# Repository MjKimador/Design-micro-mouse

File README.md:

This project includes two subsystems.
The power subsytem has files named with the suffix Power.
The sensing subsystems has files named with suffix Sensing.
There are two branches through which changes are made and the main branch holds files for both sensing subsystem and power subsystem.

For the Power Subsystem:
This system has been designed to provide power to the micro mouse system. It is designed using kiCad and to open the file you can open the .pro file and you will haev the entire project including the pcb files and schematic. The files used for ordering which inlude BOM files and all other files are not included in this folder but the project has all fields filled makingh it possible for all required files to be opened with ease.

For the Sensing Subsystem:
The subsystem serves as the sensory "eyes" of the micromouse, detecting obstacles in its path and facilitating navigation. It integrates easily with other features, ensuring efficient power usage and reliable obstacle detection within budgetary constraints.The design was done using kicad .The documents included are pcb ,schenatic and datasheet of components used.

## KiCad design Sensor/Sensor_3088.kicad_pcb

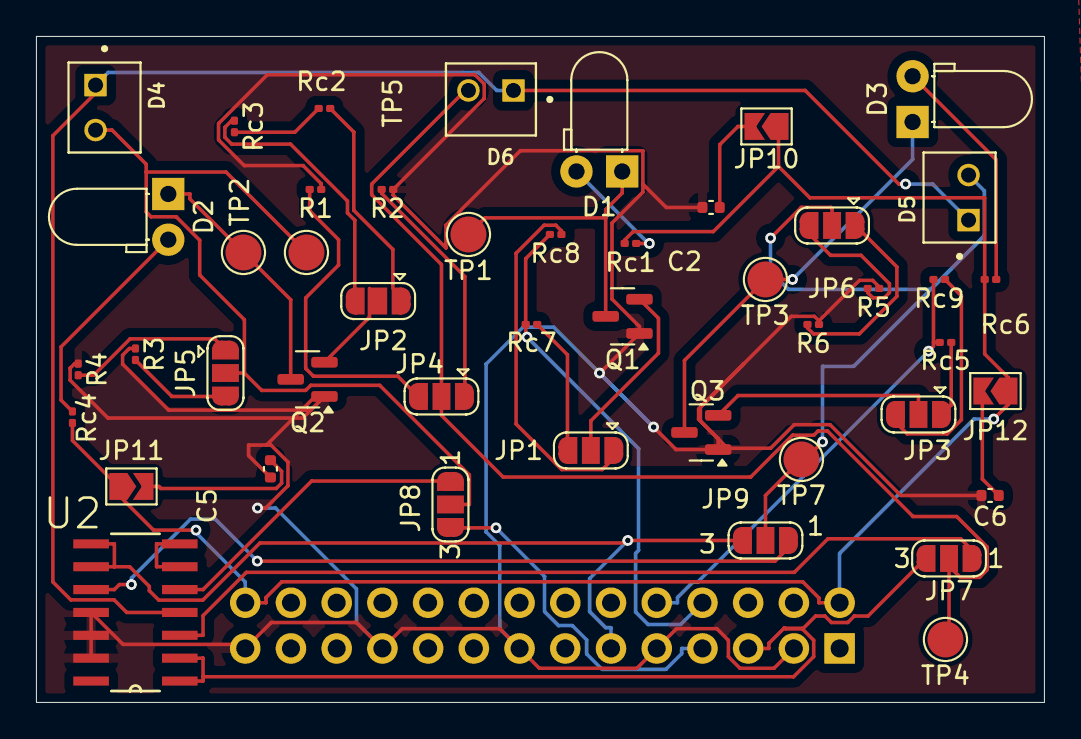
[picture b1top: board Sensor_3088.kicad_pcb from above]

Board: 2 copper layers, 56.0 x 37.0 mm, 47 parts (1 on the bottom side), 40 nets.

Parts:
C2, C5, C6: 10n; C_0402_1005Metric
D1, D2, D3: TSAL4400; LED_D3.0mm_Horizontal_O1.27mm_Z2.0mm_IRBlack
D4, D5, D6: BPW41N; DIO_BPW41N
J2: Conn_02x14_Odd_Even; PinHeader_2x14_P2.54mm_Vertical
JP1, JP2, JP3, JP4, JP5, JP6: SolderJumper_3_Open; SolderJumper-3_P1.3mm_Open_RoundedPad1.0x1.5mm
JP7, JP8, JP9: SolderJumper_3_Open; SolderJumper-3_P1.3mm_Open_RoundedPad1.0x1.5mm_NumberLabels
JP10, JP11, JP12: SolderJumper_2_Open; SolderJumper-2_P1.3mm_Open_TrianglePad1.0x1.5mm
Q1, Q2, Q3: SS8050; SOT-23
R1, R3, R5: 10k; R_0201_0603Metric
R2, R4, R6: 150k; R_0201_0603Metric
Rc1, Rc4, Rc6: 20; R_0201_0603Metric
Rc2, Rc5, Rc8: 1k; R_0201_0603Metric
Rc3, Rc7, Rc9: 470; R_0201_0603Metric
TP1, TP2, TP3, TP4, TP5, TP7: TestPoint; TestPoint_Pad_D2.0mm
U2: LM324DT; SOIC127P600X175-14N

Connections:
3V3: J2.2, J2.28, JP10.1 (A), JP11.1 (A), JP12.1 (A), Rc1.2, Rc4.2, Rc6.2
+3V3: D4.C, D5.C, D6.C, U2.4 (VCC+)
GND: C2.2, C5.2, C6.2, J2.3, J2.9, J2.15, J2.21, J2.27, Q1.1 (E), Q2.1 (E), Q3.1 (E), R1.1, R2.1, R3.1, R4.1, R5.1, R6.1, U2.11 (VCC-), U2.12 (POS_4), U2.13 (NEG_4)
unnamed: D1.2 (A), Rc1.1
unnamed: D1.1 (K), Q1.3 (C), TP1.1
unnamed: D2.2 (A), Rc4.1
unnamed: D2.1 (K), Q2.3 (C), TP2.1
unnamed: D3.2 (A), Rc6.1
unnamed: D3.1 (K), Q3.3 (C), TP3.1
unnamed: JP1.1 (A), Rc8.1
unnamed: JP1.3 (B), Rc7.1
unnamed: JP1.2 (C), Q1.2 (B)
unnamed: JP2.1 (A), Rc2.1
unnamed: JP2.3 (B), Rc3.1
unnamed: JP2.2 (C), Q2.2 (B)
unnamed: JP3.1 (A), Rc5.1
unnamed: JP3.3 (B), Rc9.1
unnamed: JP3.2 (C), Q3.2 (B)
unnamed: JP4.1 (A), R2.2
unnamed: JP4.3 (B), R1.2
unnamed: JP5.1 (A), R4.2
unnamed: JP5.3 (B), R3.2
unnamed: JP6.1 (A), R6.2
unnamed: JP6.3 (B), R5.2
unnamed: C2.1, JP10.2 (B)
unnamed: C5.1, JP11.2 (B)
unnamed: C6.1, JP12.2 (B)
unnamed: U2.6 (NEG_2), U2.7 (OUT2)
OUT1: D6.A, JP4.2 (C), JP7.2 (C), TP4.1
Output2: D4.A, JP5.2 (C), JP8.2 (C), TP5.1
Output3: D5.A, JP6.2 (C), JP9.2 (C), TP7.1
PA3: J2.5, JP7.3 (B), U2.1 (OUT1), U2.2 (NEG_1)
PA4: J2.7, JP8.3 (B)
PA5: J2.11, JP9.3 (B), U2.8 (OUT3), U2.9 (NEG3)
PE13: Rc2.2, Rc3.2
PE14: J2.10, Rc5.2, Rc9.2
PE15: J2.8, Rc7.2, Rc8.2
POS1: JP7.1 (A), U2.3 (POS_1)
POS2: JP8.1 (A), U2.5 (POS_2)
POS3: JP9.1 (A), U2.10 (POS_3)

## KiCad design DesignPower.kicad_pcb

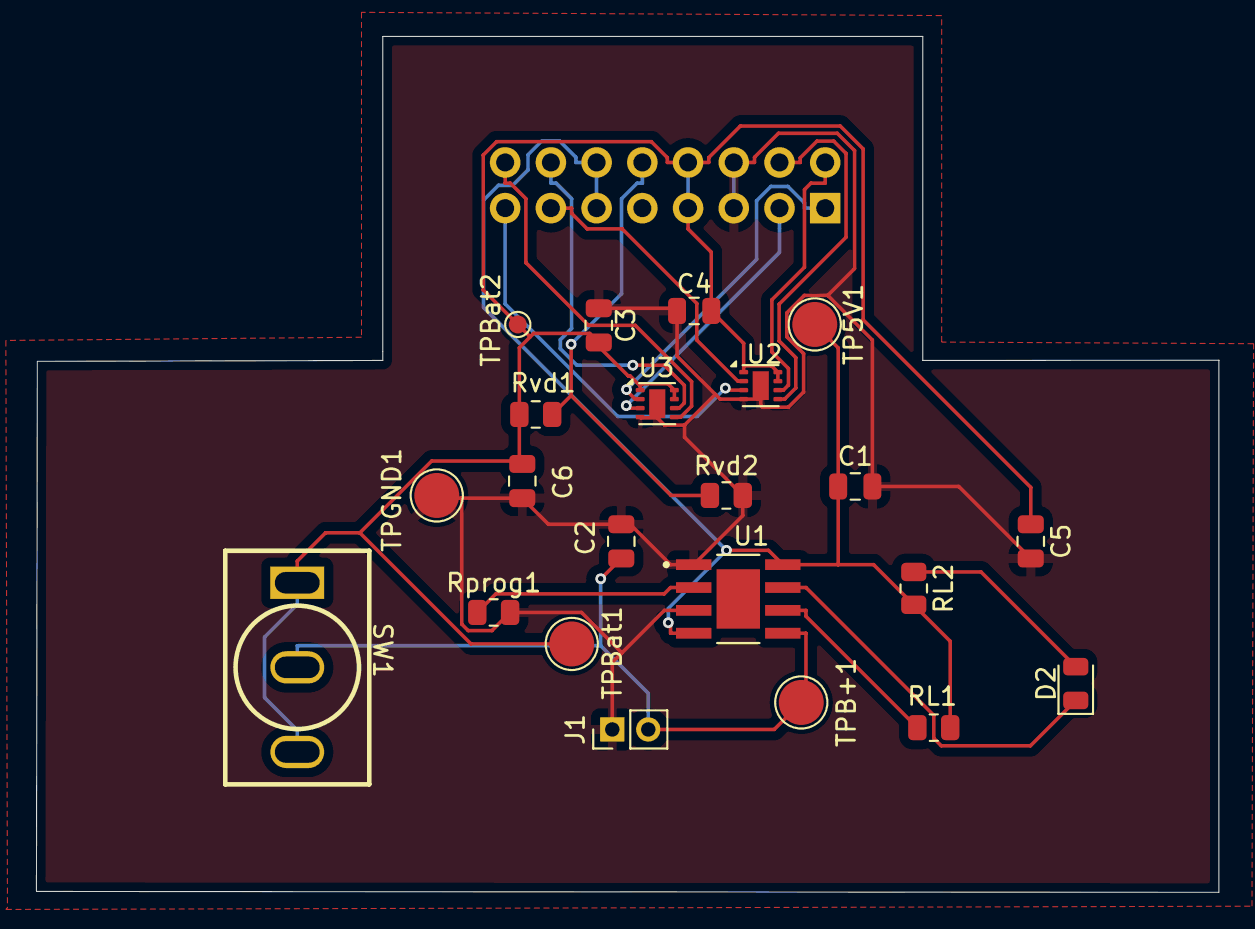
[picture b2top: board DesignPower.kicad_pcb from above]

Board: 2 copper layers, 65.7 x 47.6 mm, 23 parts (1 on the bottom side), 17 nets.

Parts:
C1, C2: 10uf; C_0805_2012Metric
C3, C4, C5, C6: 100nF; C_0805_2012Metric
D2: LED; LED_0805_2012Metric
J1: Conn_01x02_Pin; PinHeader_1x02_P2.00mm_Vertical
J2: Conn_02x08_Odd_Even; PinHeader_2x08_P2.54mm_Vertical
RL1, RL2: 1000; R_0805_2012Metric
Rprog1: 6800; R_0805_2012Metric
Rvd1: 200k; R_0805_2012Metric
Rvd2: 510k; R_0805_2012Metric
SW1: SW-TH_MT-0-103-A101-M200-RS
TP5V1: 5V-bat test; TestPoint_Pad_D2.5mm
TPB+1: TestPoint; TestPoint_Pad_D2.5mm
TPBat1: TestPoint; TestPoint_Pad_D2.5mm
TPBat2: BATT; TestPoint_Pad_D1.0mm
TPGND1: TestPoint; TestPoint_Pad_D2.5mm
U1: TP4056; SOIC127P600X175-9N
U2, U3: DRV8837; WSON-8-1EP_2x2mm_P0.5mm_EP0.9x1.6mm

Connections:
+5V: C1.1, J2.11, J2.12, RL1.2, RL2.2, TP5V1.1, U1.4 (VCC), U1.8 (CE)
/B+: C2.2, J1.2, SW1.2, TPB+1.1, U1.5 (BAT)
BATT: C3.1, C4.1, C5.1, C6.1, J2.7, J2.8, Rvd1.1, SW1.1, SW1.3, TPBat1.1, TPBat2.1, U2.1 (VM), U2.7 (~SLEEP), U2.8 (VCC), U3.1 (VM), U3.7 (~SLEEP), U3.8 (VCC)
BATT_ADC: J2.10, Rvd1.2, Rvd2.1
GND: C1.2, C2.1, C3.2, C4.2, C5.2, C6.2, J1.1, J2.5, J2.6, Rprog1.2, Rvd2.2, TPGND1.1, U1.1 (TEMP), U1.3 (GND), U2.4 (GND), U2.9 (GND), U3.4 (GND), U3.9 (GND)
Motor1_A: J2.13, U2.2 (OUT1)
Motor1_B: J2.15, U2.3 (OUT2)
Motor2_A: J2.1, U3.2 (OUT1)
Motor2_B: J2.3, U3.3 (OUT2)
unnamed: D2.2 (A), RL2.1
unnamed: D2.1 (K), U1.7 (*CHRG)
unnamed: RL1.1, U1.6 (*STDBY)
unnamed: Rprog1.1, U1.2 (PROG)
PWM1: J2.2, U2.6 (IN1)
PWM2: J2.4, U2.5 (IN2)
PWM3: J2.14, U3.6 (IN1)
PWM4: J2.16, U3.5 (IN2)

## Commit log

2024-04-20 test
2024-04-20 initial
2024-04-20 Added a new motor driver
2024-04-20 added jumper for current and labels on schematic logic
2024-04-24 Add files via upload
    sensor subsystem files.
2024-04-24 Update README.md
    Added information on sensor subsystem
2024-05-17 code for demo
    code for demo
